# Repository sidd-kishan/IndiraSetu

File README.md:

# IndraSetu
## pi pico <-> ft232h
#### GPIO2 -> CLKOUT
#### GPIO3 -> RXF#
#### GPIO4 -> TXE#

#### GPIO5 -> OE#
#### GPIO6 -> RD#
#### GPIO7 -> WR#

#### GPIO8 -> BIT0

#### 3v3  + 3.3v -> ili9341 VCC -> LED ( this is for the lcd back light will be only be labled as led ) needs 3v3 volts from both the chips to balance current draw.

## pi pico -> ili9341 

Sending data which is emiting from pc through ft232h into pi pico with the help of PIO state machine

(PC + FT232H) -> Pi Pico

https://ftdichip.com/wp-content/uploads/2023/09/DS_FT232H.pdf page9

https://ftdichip.com/wp-content/uploads/2020/08/TN_167_FIFO_Basics.pdf page15

Refrences:-
[AN130](https://ftdichip.com/wp-content/uploads/2020/08/AN_130_FT2232H_Used_In_FT245-Synchronous-FIFO-Mode.pdf)
[AN135](https://www.ftdichip.com/Documents/AppNotes/AN_135_MPSSE_Basics.pdf)
[AN165](https://www.ftdichip.com/Documents/AppNotes/AN_165_Establishing_Synchronous_245_FIFO_Communications_using_a_Morph-IC-II.pdf)
[AN167](https://ftdichip.com/wp-content/uploads/2020/08/TN_167_FIFO_Basics.pdf)
[AN124](https://www.ftdichip.cn/Support/Documents/AppNotes/oldAN_124_User_Guide_For_FT_PROG.pdf)

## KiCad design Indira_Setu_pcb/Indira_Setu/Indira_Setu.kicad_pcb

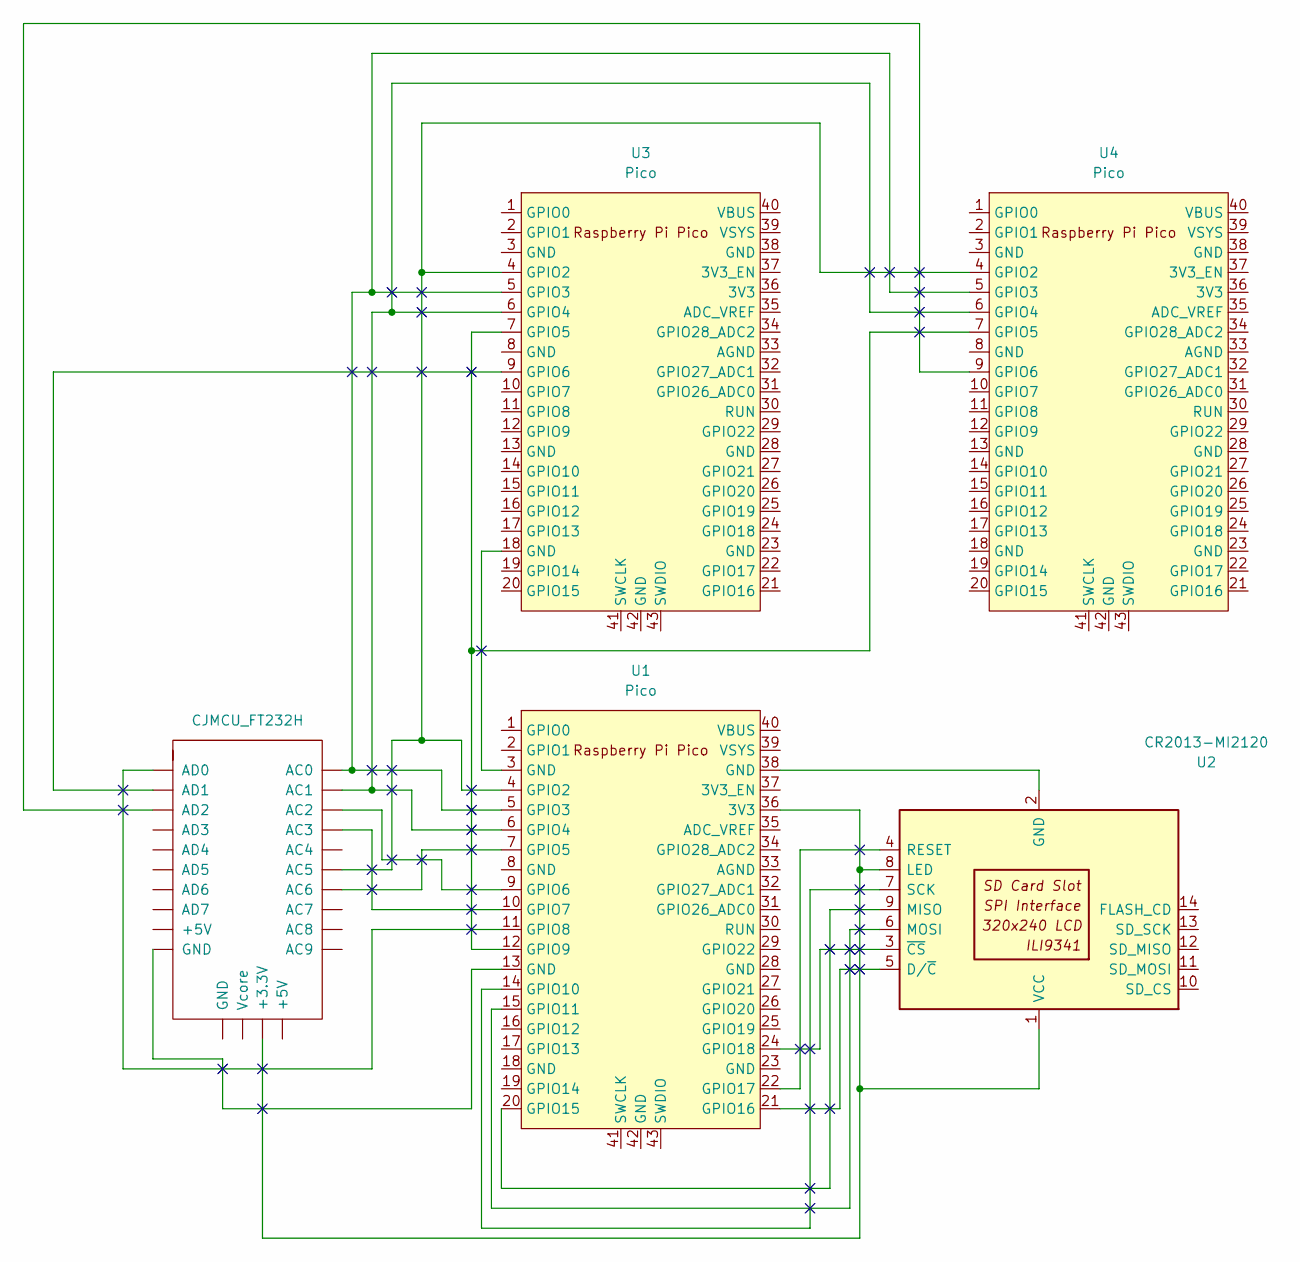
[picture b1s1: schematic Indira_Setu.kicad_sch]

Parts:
CJMCU_FT1: CJMCU_FT232H
U1, U3, U4: Pico; RPi_Pico_SMD_TH
U2: CR2013-MI2120

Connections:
unnamed: CJMCU_FT1.GND1 (GND), U1.13 (GND)
unnamed: CJMCU_FT1.+3.3V, U1.36 (3V3), U2.1 (VCC), U2.8 (LED)
unnamed: U1.3 (GND), U3.18 (GND)
unnamed: CJMCU_FT1.AC5, U1.4 (GPIO2), U3.4 (GPIO2), U4.4 (GPIO2)
unnamed: CJMCU_FT1.AC0, U1.5 (GPIO3), U3.5 (GPIO3), U4.5 (GPIO3)
unnamed: CJMCU_FT1.AC1, U1.6 (GPIO4), U3.6 (GPIO4), U4.6 (GPIO4)
unnamed: CJMCU_FT1.AC6, U1.7 (GPIO5)
unnamed: CJMCU_FT1.AC2, U1.9 (GPIO6)
unnamed: CJMCU_FT1.AC3, U1.10 (GPIO7)
unnamed: CJMCU_FT1.AD0, U1.11 (GPIO8)
unnamed: U1.12 (GPIO9), U3.7 (GPIO5), U4.7 (GPIO5)
unnamed: U1.14 (GPIO10), U2.7 (SCK)
unnamed: U1.15 (GPIO11), U2.6 (MOSI)
unnamed: U1.20 (GPIO15), U2.9 (MISO)
unnamed: U1.21 (GPIO16), U2.5 (D/~C)
unnamed: U1.22 (GPIO17), U2.4 (RESET)
unnamed: U1.24 (GPIO18), U2.3 (~CS)
unnamed: U1.38 (GND), U2.2 (GND)
unnamed: CJMCU_FT1.AD1, U3.9 (GPIO6)
unnamed: CJMCU_FT1.AD2, U4.9 (GPIO6)

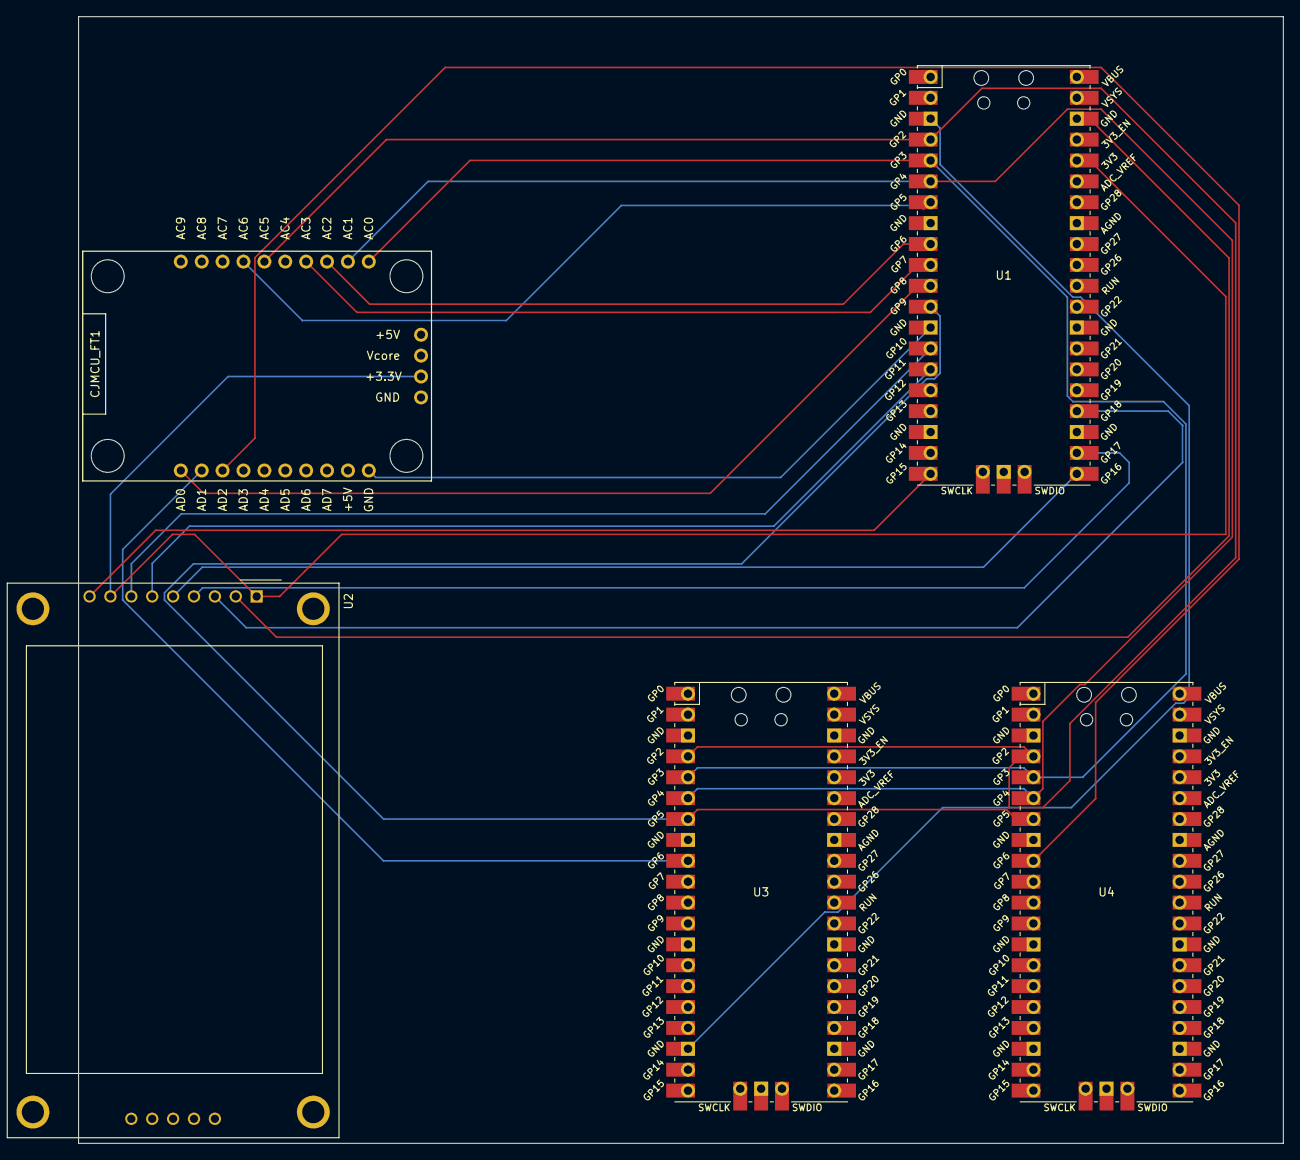
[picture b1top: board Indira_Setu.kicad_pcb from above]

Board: 2 copper layers, 146.5 x 137.0 mm, 5 parts (0 on the bottom side), 20 nets.

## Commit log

2025-01-21 Create PicoCoreInjestion.py
    RP2040 PIO code to take data from FT232H at 60MHZ in SYNC FIFO mode at 480MbPS
2025-01-21 Create FTDI-Sender.cpp
    It arranges "hello world" in a buffer of 1024 bytes and sends 1st 255 bytes over and over again as 255 = 32 bytes which is the size of the rx fifo in pi pico pio side not any other reason.
    h - 01101000
    e - 01100101
    l - 01101100
    l - 01101100
    o - 01101111
2025-02-14 Flash this config file with ft_prog program
2025-02-14 The output is aligned to 32 bits
2025-02-16 If OE#, RD# and WR# is wired all wrong
2025-03-02 Update PicoCoreInjestion.py
    started to put locks in place
2025-03-02 Update FTDI-Sender.cpp
    sync pattern added
2025-04-16 Update PicoCoreInjestion.py
    Started to chase the falling edge much more stable
2025-04-16 Update FTDI-Sender.cpp
    relying solely upon the flashed eeprom no further resets for added stability
2025-04-16 Update PicoCoreInjestion.py
    able to find pattern more frequently
2025-04-19 Update PicoCoreInjestion.py
    1 bit error correction added
2025-04-19 Update FTDI-Sender.cpp
    added some labels to the code
2025-04-21 Update PicoCoreInjestion.py
    Interrupt driven code pattern for efficient data acquisition
2025-04-21 Update PicoCoreInjestion.py
    just juggling for stability
2025-04-22 Update PicoCoreInjestion.py
    Trying over sampling
    >>> %Run -c $EDITOR_CONTENT
    MPY: soft reboot
    11100010100100010001100101001011
    11001100110111100000000011110
    11011011110011001001100110011001
2025-04-22 Update PicoCoreInjestion.py
    01001000 : H
    01100101 : e
    01101111 : o
    01100011 : c
    01111001 : y
    00000011 : 
2025-04-23 Update PicoCoreInjestion.py
    Debugging code added I think the wiring is short
    ------------------
    Pin 3 went LOW!
    -1
    ***********************
    -1
2025-04-24 Update PicoCoreInjestion.py
    we need to make it 32 to not loose on 8 bits across fifo
2025-04-26 Update PicoCoreInjestion.py
    >>> %Run -c $EDITOR_CONTENT
    MPY: soft reboot
    ------------------
    ------------------
    ------------------
    ------------------
2025-04-26 Update PicoCoreInjestion.py
    pio stability added
2025-04-26 Update FTDI-Sender.cpp
    faster test
2025-04-28 Update PicoCoreInjestion.py
    differential pattern of 10101010 and 01010101 start of the header. 8 is good
2025-04-28 Update FTDI-Sender.cpp
    differential bytes sent start of the message 10101010 and 01010101
2025-04-28 required files
2025-04-29 Update PicoCoreInjestion.py
    bit rotation added trying to get rid of the first 2 dirty bits
2025-05-03 Update PicoCoreInjestion.py
    Refactor
2025-05-03 Update FTDI-Sender.cpp
    Refactor
2025-05-04 Create pattern_gen.c
    gcc pattern_gen.c -o text
    ./text "Hello world" 1024 --prefix "0xFF,0x00,0xFF,0x00,0xFF,0x00,0xFF,0x00" --suffix "0x00,0xFF,0x00,0xFF,0x00,0xFF,0x00,0xFF"
    Repeating pattern (prefix + message + suffix) to fill buffer.
    TxBuffer[] = {
    0xFF, 0x00, 0xFF, 0x00, 0xFF, 0x00, 0xFF, 0x00, 0x00, 0xFF, 0x00, 0x00, 0xFF, 0x00, 0x00, 0x00, // byte #1 ('H')
    0x00, 0xFF, 0xFF, 0x00, 0x00, 0xFF, 0x00, 0xFF, // byte #2 ('e')
2025-05-04 Update pattern_gen.c
    gcc pattern_gen.c -o text
    ./text "Aa0Aa1Aa2Aa3Aa4Aa5Aa6Aa7Aa8Aa9Ab0Ab1Ab2Ab3Ab4Ab5Ab6Ab7Ab8Ab9Ac0Ac1Ac2Ac3Ac4Ac5Ac6Ac7Ac8Ac9Ad0Ad1Ad2Ad3Ad4Ad5Ad6Ad7Ad8Ad9Ae0Ae1Ae" 1024 --pattern "0xFF,0x00,0x00,0x00,0x00,0x00,0xFF,0x00,0xFF,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
    Input is sufficient to fill TxBuffer without repetition.
    TxBuffer[] = {
    0x00, 0xFF, 0x00, 0x00, 0x00, 0x00, 0x00, 0xFF // byte #1 ('A')
    0x00, 0xFF, 0xFF, 0x00, 0x00, 0x00, 0x00, 0xFF // byte #2 ('a')
2025-05-05 Update pattern_gen.c
    gcc pattern_gen.c -o text
    ./text "Hello World" 1024
    TxBuffer[] = {
    0x00, 0xFF, 0x00, 0x00, 0xFF, 0x00, 0x00, 0x00, // 'H'
    0x00, 0xFF, 0xFF, 0x00, 0x00, 0xFF, 0x00, 0xFF, // 'e'
    0x00, 0xFF, 0xFF, 0x00, 0xFF, 0xFF, 0x00, 0x00, // 'l'
2025-05-05 Update PicoCoreInjestion.py
    11 byte packet with 1 byte crc_8 matching added
2025-05-05 Update FTDI-Sender.cpp
    ./text "Hello World0" 1024 --prefix "0xFF,0X00,0XFF,0x00,0x00,0xFF,0x00,0XFF" --suffix "0x00,0xFF,0x00,0xFF,0xFF,0x00,0xFF,0x00" --pattern "0x00,0xFF,0x00,0x00,0xFF,0x00,0x00,0x00"
2025-05-05 Update FTDI-Sender.cpp
    added pattern gen to the transmission code
2025-05-07 Update PicoCoreInjestion.py
    Walk and talk
2025-05-08 Update PicoCoreInjestion.py
    Frame Buffering added
2025-05-08 Update FTDI-Sender.cpp
    building a message queue
2025-05-09 Create objfile.cpp
    to render and send triangles.
2025-05-09 Update PicoCoreInjestion.py
    added a byte
2025-05-09 Update FTDI-Sender.cpp
    added a byte to template
2025-05-09 Update PicoCoreInjestion.py
    efficiency improvement
2025-05-09 Update FTDI-Sender.cpp
    eff improve
2025-05-09 Update PicoCoreInjestion.py
    eff improve
2025-05-10 Update FTDI-Sender.cpp
    Triangle extraction added
2025-05-10 Update FTDI-Sender.cpp
    triag print
2025-05-10 Update PicoCoreInjestion.py
    hex encoded print
2025-05-10 Update FTDI-Sender.cpp
    getting the vertices to near to the dispatch code
2025-05-11 Update FTDI-Sender.cpp
    Dynamic input length
2025-05-11 Update FTDI-Sender.cpp
    grouping triangles for dispatch
2025-05-12 Update FTDI-Sender.cpp
    able to send 1 byte
2025-05-12 Update PicoCoreInjestion.py
    extracting one byte
2025-05-13 Update objfile.cpp
    all int
2025-05-13 Update FTDI-Sender.cpp
    try reading from a file
2025-05-13 Update FTDI-Sender.cpp
    Importing data from csv file.
2025-05-13 Update PicoCoreInjestion.py
    Slow Read achieved, lots of noise following is the packet summary:-
    24.47%
    hit: 1 bytes on 8 channels recv: 14 miss: 7 and crc8 verified:150 83 146 87 146 90 79 159 76 168 78 162 79 243
    14.00651
    hit: 2 bytes on 8 channels recv: 28 miss: 24 and crc8 verified:131 94 134 100 135 114 227 172 78 174 83 174 82 47
    14.07472
2025-05-13 Update FTDI-Sender.cpp
    csv read and send
2025-05-13 Update objfile.cpp
    data.csv writer complete
2025-05-13 Add files via upload
    wolf.obj to csv
2025-05-14 Update FTDI-Sender.cpp
    pre render and dispatch with random seed increments
2025-05-14 Update PicoCoreInjestion.py
    rendering to SPI LCD added
2025-05-14 Update objfile.cpp
    demo adjustments
2025-05-14 Update objfile.cpp
    demo adjustment
2025-05-14 Update FTDI-Sender.cpp
    sending loop over data
2025-05-15 Update objfile.cpp
    adjusting for color in the correct format.
2025-05-15 Update PicoCoreInjestion.py
    some optimize
2025-05-15 Update objfile.cpp
    2 crc is better than one for each trigs
2025-05-15 Update FTDI-Sender.cpp
    sync
2025-05-16 Update PicoCoreInjestion.py
    need to add feedback for repeating filtered triangle
2025-05-17 Update PicoCoreInjestion.py
    PIO fast pooling
2025-05-17 Update FTDI-Sender.cpp
    fast pooling
2025-05-18 PCB file added
